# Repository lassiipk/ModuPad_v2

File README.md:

# ModuPad_v2

Improved Version of my ModuPad v1, With 3 Push Button rotary encoders, 25 Key switches, nice!nano MCU, and nice!view display.

---

---

## Schematic

---

## PCB

<!--  -->

---

## CAD

| Bottom | Full-CAD | Upper-Plate | 
| ------ | -------- | ----------- |
|  |  |  |

---

## BOM

**1 USD = 279.55 PKR**

> [Cart_Images](https://github.com/lassiipk/ModuPad_v2/tree/main/BOM/Cart_Images)
>
> [BOM.csv](https://github.com/lassiipk/ModuPad_v2/blob/main/BOM/BOM.csv)
>
> [BOM Folder](https://github.com/lassiipk/ModuPad_v2/tree/main/BOM/)

| Priority | Item                          | Qty | Unit Price | Shipping  | Total     | Notes               | Ordering Site    |
| -------- | ----------------------------- | --- | ---------- | --------- | --------- | ------------------- | ---------------- |
| 1        | PCB (Printed Circuit Board)   |  1  | US $8.40   | US $10.30 | US $18.70 | PCB                 | [JCLPCB](https://github.com/lassiipk/ModuPad_v2/blob/main/BOM/Cart_Images/JLCPCB_Screenshot-2026-03-17-183200.png) | 
| 2        | 3D Printed Case               |  1  | US $0.00   | US $12.00 | US $12.00 | Case / Knobs        | [#printing-legion](https://hackclub.enterprise.slack.com/archives/C083P4FJM46) |
| 3        | 3.7V 800mAh Battery           |  1  | US $1.79   | US $0.91  | US $2.71  | Wireless Connection | [Daraz](https://www.daraz.pk//products/i422858128-s2001359619.html?spm=a2o42.cart.0.0.af8f7d68YCkevZ&urlFlag=true) |
| 4        | nice!nano_v2.0 (NRF52840)     |  1  | US $3.30   | Free      | US $3.30  | MCU                 | [AliExpress](https://www.aliexpress.com/item/1005009516681283.html?spm=a2g0o.cart.0.0.7f5938da0jaPUj&mp=1&pdp_npi=6%40dis%21USD%21USD%203.30%21USD%203.30%21%21USD%203.30%21%21%21%40210156fc17737566309362930edfd4%2112000049341617471%21ct%21PK%216395474379%21%211%210%21) |
| 5        | 0.91 Inch 128x32 OLED Display |  1  | US $2.68   | Free      | US $2.68  | 128x32 OLED Display | [AliExpress](https://www.aliexpress.com/item/1005008640132638.html?spm=a2g0o.cart.0.0.7f5938da0jaPUj&mp=1&pdp_npi=6%40dis%21USD%21USD%202.84%21USD%202.68%21%21USD%202.68%21%21%21%40210156fc17737566288612823edfd4%2112000046056501838%21ct%21PK%216395474379%21%211%210%21) |
| 6        | Cherry MX Style Switches      |  1  | US $3.24   | Free      | US $3.24  | Switches            | [A;iExpress](https://www.aliexpress.com/item/1005010772946238.html?spm=a2g0o.cart.0.0.7f5938da0jaPUj&mp=1&pdp_npi=6%40dis%21USD%21USD%203.24%21USD%203.24%21%21USD%203.24%21%21%21%40210156fc17737566288612823edfd4%2112000053464130840%21ct%21PK%216395474379%21%211%210%21) |
| 7        | SK6812 MINI-E RGB LEDs        |  1  | US $3.69   | Free      | US $3.69  | RGB                 | [AliExpress](https://www.aliexpress.com/item/1005005193716172.html?spm=a2g0o.cart.0.0.744038da23sMVn&mp=1&pdp_npi=6%40dis%21USD%21USD%203.86%21USD%203.86%21%21USD%203.86%21%21%21%4021010d9017721244036344079e42d2%2112000032072424634%21ct%21PK%216395474379%21%211%210%21) |
| 8        | EC11 Rotary Encoders          |  1  | US $2.55   | Free      | US $2.55  | Rotary Encoders     | [AliExpress](https://www.aliexpress.com/item/1005007644083514.html?spm=a2g0o.cart.0.0.744038da23sMVn&mp=1&pdp_npi=6%40dis%21USD%21USD%202.65%21USD%202.65%21%21USD%202.65%21%21%21%4021010d9017721245116916843e42d2%2112000041630839426%21ct%21PK%216395474379%21%211%210%21) |
| 9        | 1N4148W SMD Diodes            |  1  | US $1.60   | Free      | US $1.60  | 28 diodes           | [AliExpress](https://www.aliexpress.com/item/1005007160563285.html?spm=a2g0o.cart.0.0.7f5938da0jaPUj&mp=1&pdp_npi=6%40dis%21USD%21USD%202.21%21USD%201.60%21%21USD%201.60%21%21%21%40210156fc17737566288612823edfd4%2112000039653324544%21ct%21PK%216395474379%21%211%210%21) |
| 10       | Kailh Hotswap Sockets         |  1  | US $2.82   | Free      | US $2.82  | Hotswap Sockets     | [AliExpress](https://www.aliexpress.com/item/1005009794038277.html?spm=a2g0o.cart.0.0.7f5938da0jaPUj&mp=1&pdp_npi=6%40dis%21USD%21USD%205.75%21USD%202.82%21%21USD%202.82%21%21%21%40210156fc17737566288612823edfd4%2112000050182431031%21ct%21PK%216395474379%21%211%210%21) |
| 11       | DSA Keycaps                   |  1  | US $5.00   | Free      | US $5.00  | 25 keycaps          | [AliExpress](https://www.aliexpress.com/item/32842379355.html?spm=a2g0o.cart.0.0.7f5938da0jaPUj&mp=1&pdp_npi=6%40dis%21USD%21USD%205.28%21USD%205.28%21%21USD%205.28%21%21%21%40210156fc17737566309362930edfd4%2110000001467765234%21ct%21PK%216395474379%21%211%210%21) |
| 12       | Power Switch                  |  1  | US $1.95   | Free      | US $1.95  | Power cutoff        | [AliExpress](https://www.aliexpress.com/item/1005007372534237.html?spm=a2g0o.cart.0.0.7f5938da0jaPUj&mp=1&pdp_npi=6%40dis%21USD%21USD%202.95%21USD%201.89%21%21USD%201.89%21%21%21%40210156fc17737566309362930edfd4%2112000040538852784%21ct%21PK%216395474379%21%211%210%21) |
| 13       | Battery Jack                  |  1  | US $1.66   | Free      | US $1.66  | Battery connection  | [AliExpress](https://www.aliexpress.com/item/1005004955655144.html?spm=a2g0o.cart.0.0.7f5938da0jaPUj&mp=1&pdp_npi=6%40dis%21USD%21USD%201.66%21USD%201.66%21%21USD%201.66%21%21%21%40210156fc17737566288612823edfd4%2112000031146362164%21ct%21PK%216395474379%21%211%210%21) |
| 14       | Reset Button                  |  1  | US $1.72   | Free      | US $1.72  | Reset For MCU       | [AliExpress](https://www.aliexpress.com/item/1005009331265393.html?spm=a2g0o.cart.0.0.7f5938da0jaPUj&mp=1&pdp_npi=6%40dis%21USD%21USD%201.72%21USD%201.72%21%21USD%201.72%21%21%21%40210156fc17737566288612823edfd4%2112000048778390261%21ct%21PK%216395474379%21%211%210%21) |
| 15       | 330R Resistor                 |  1  | US $2.27   | Free      | US $2.27  | Resistor            | [AliExpress](https://www.aliexpress.com/item/1005007043943146.html?spm=a2g0o.cart.0.0.7f5938da0jaPUj&mp=1&pdp_npi=6%40dis%21USD%21USD%202.88%21USD%202.28%21%21USD%202.28%21%21%21%40210156fc17737566288612823edfd4%2112000039203406400%21ct%21PK%216395474379%21%211%210%21) |
| 16       | 470UF Capacitor               |  1  | US $2.93   | Free      | US $2.93  | Capacitor           | [AliExpress](https://www.aliexpress.com/item/1005008498295736.html?spm=a2g0o.cart.0.0.7f5938da0jaPUj&mp=1&pdp_npi=6%40dis%21USD%21USD%203.05%21USD%202.85%21%21USD%202.85%21%21%21%40210156fc17737566288612823edfd4%2112000045532285458%21ct%21PK%216395474379%21%211%210%21) |
| 17       | M2/8mm Standoffs              |  1  | US $3.50   | Free      | US $3.50  | Mounting            | [AliExpress](https://www.aliexpress.com/item/1005008713639234.html?spm=a2g0o.cart.0.0.7f5938da0jaPUj&mp=1&pdp_npi=6%40dis%21USD%21USD%203.77%21USD%203.50%21%21USD%203.50%21%21%21%40210156fc17737566288612823edfd4%2112000046354950634%21ct%21PK%216395474379%21%211%210%21) |
| 18       | M2/4mm Screws                 |  1  | US $1.11   | Free      | US $1.11  | Mounting            | [AliExpress](https://www.aliexpress.com/item/1005003604942716.html?spm=a2g0o.cart.0.0.7f5938da0jaPUj&mp=1&pdp_npi=6%40dis%21USD%21USD%201.11%21USD%201.11%21%21USD%201.11%21%21%21%40210156fc17737566288612823edfd4%2112000026464812448%21ct%21PK%216395474379%21%211%210%21&pdp_ext_f=%7B%22cart2PdpParams%22%3A%7B%22pdpBusinessMode%22%3A%22retail%22%7D%7D) |

---    

> **AliExpress-Total = US $40.17** | *incl. Shipping*
>
> **#Printing-Legion = US $10** | *incl. Shipping*
>
> **JLCPCB-Total = US $20.00** | *incl. Shipping*
>
> **Daraz-Total = US $2.70** | *incl. Shipping*

**Total = US $73.44** | *incl. Shipping*

---

## Timeline

**Project Started:** 05-Jan 2026 | 3:40PM

**Project Ended:** 14-Feb-2026 | 5:00 PM

**Project README Entry Written:** 17-Feb 2026 | 9:00 PM

**Project Intital Submit:** Feb 17th at 9:21 PM

**Project Second submission:** Feb 27th at N/a AM (**@alexren** requested changes, Feb 19th at 2:48 AM) BOM is optimised as much I was able to!

---

## License

This project is open‑source and intended for educational and personal use.

---

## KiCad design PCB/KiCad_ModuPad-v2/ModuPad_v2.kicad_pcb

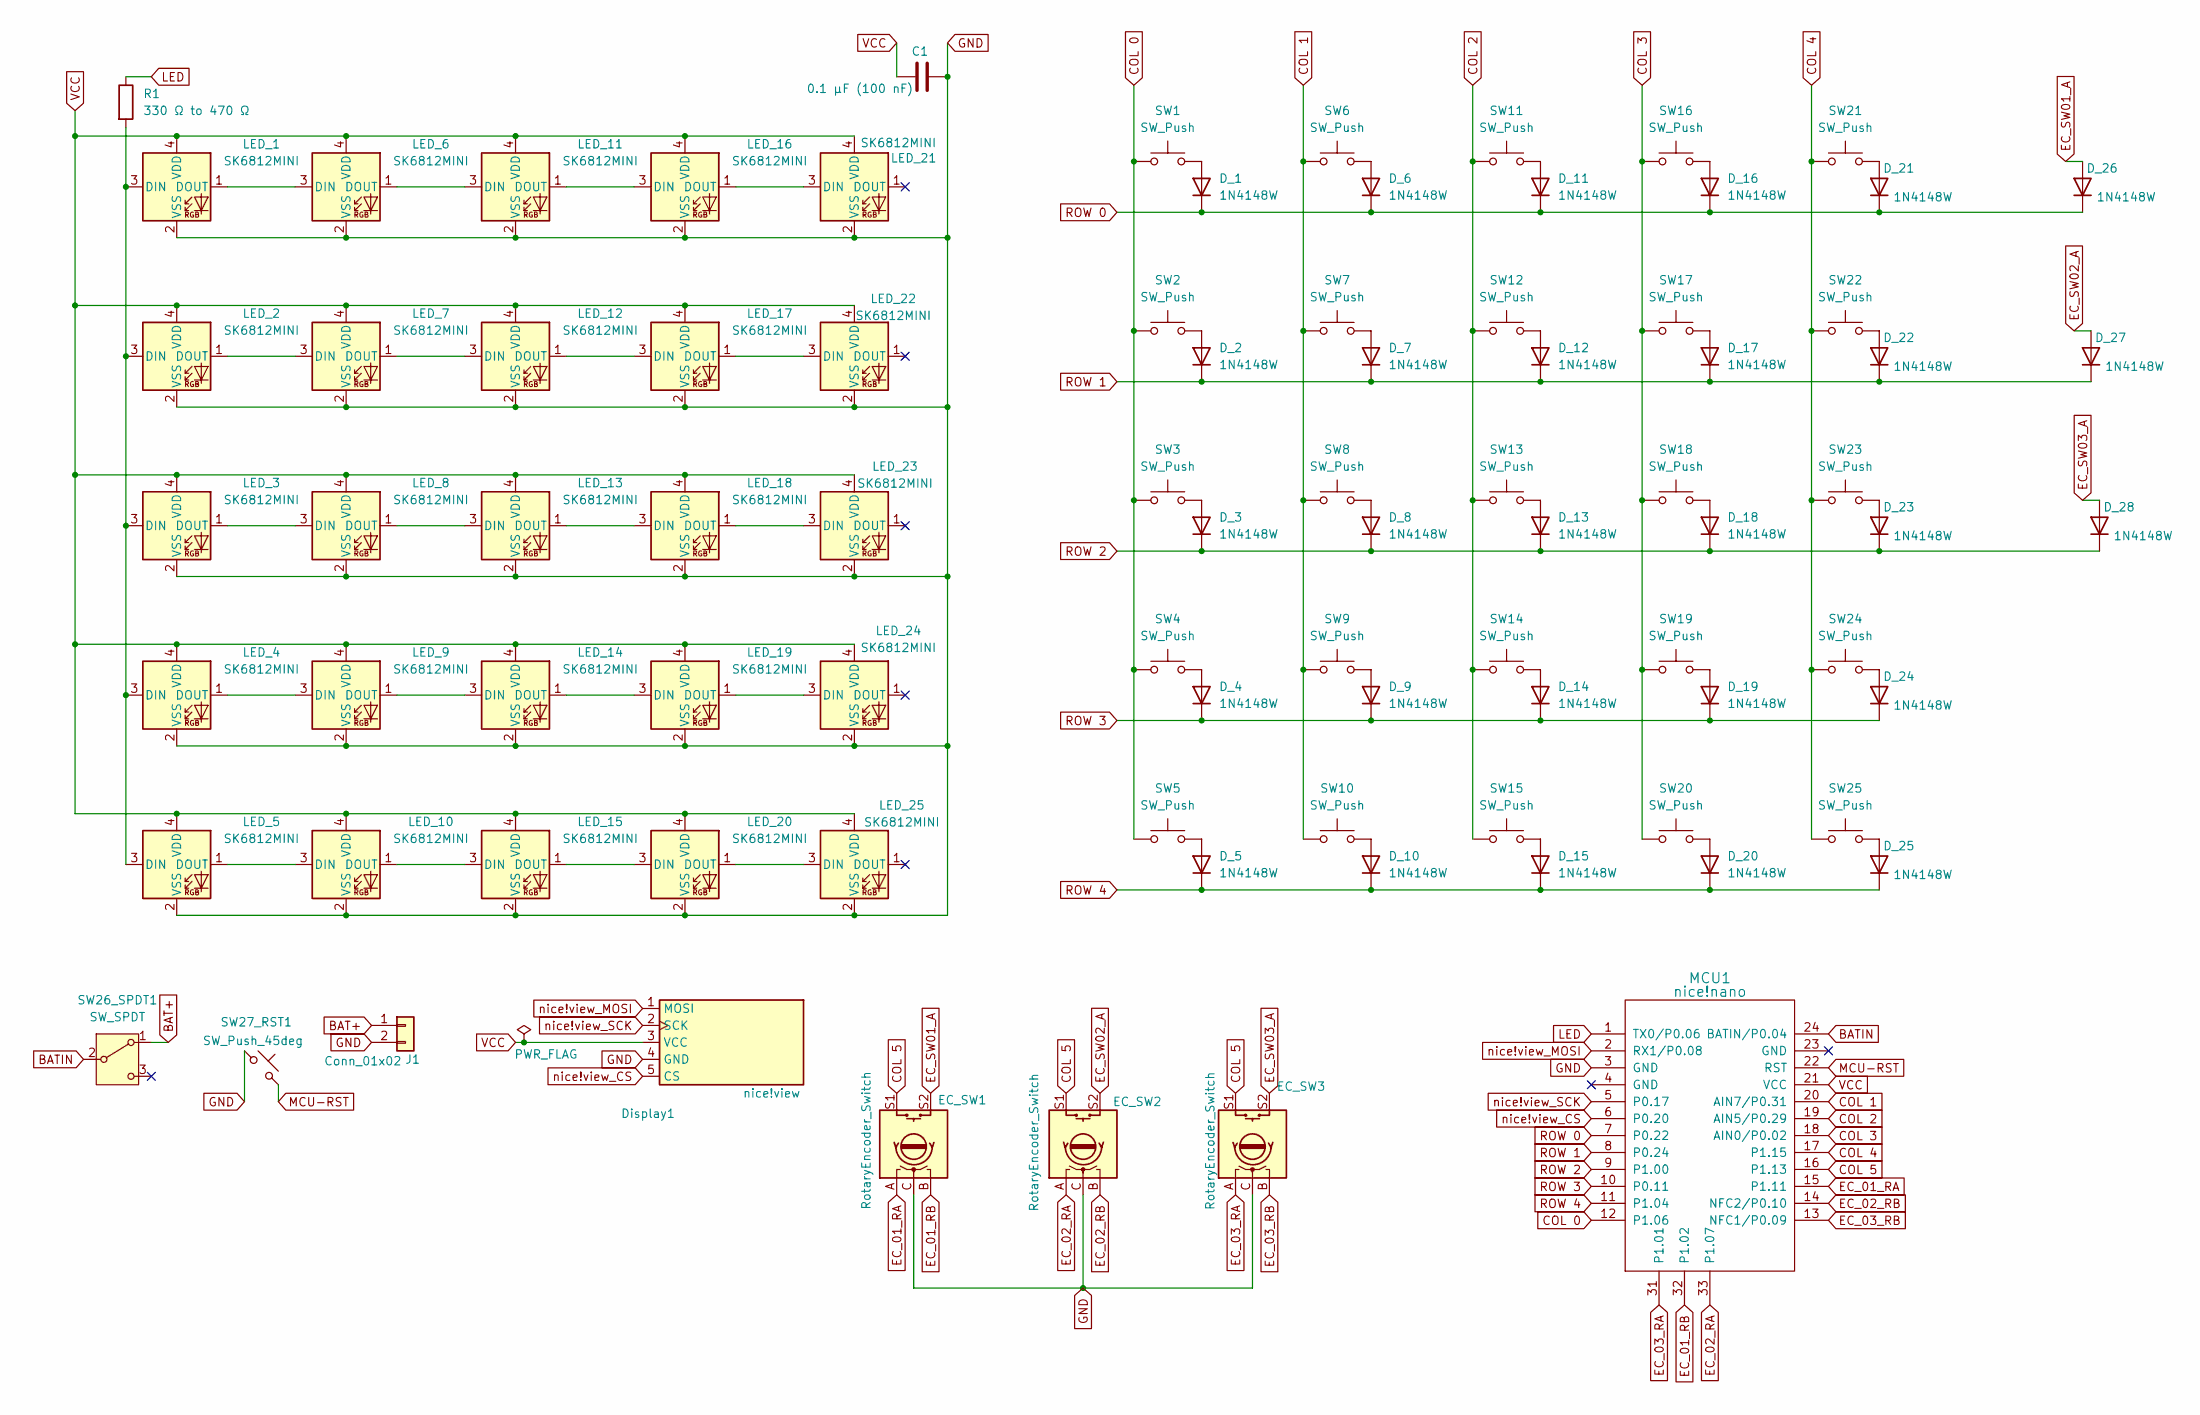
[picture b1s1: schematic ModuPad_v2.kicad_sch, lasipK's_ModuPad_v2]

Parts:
C1: 0.1 µF (100 nF); C_0603_1608Metric
D_1, D_2, D_3, D_4, D_5, D_6, D_7, D_8, D_9, D_10, D_11, D_12, D_13, D_14, D_15, D_16, D_17, D_18, D_19, D_20, D_21, D_22, D_23, D_24, D_25, D_26, D_27, D_28: 1N4148W; D_SOD-123
Display1: nice!view; nice_view
EC_SW1, EC_SW2, EC_SW3: RotaryEncoder_Switch; RotaryEncoder_Alps_EC11E-Switch_Vertical_H20mm_CircularMoun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
J1: Conn_01x02; JST_PH_S2B-PH-K_02x2.00mm_Angled
LED_1, LED_2, LED_3, LED_4, LED_5, LED_6, LED_7, LED_8, LED_9, LED_10, LED_11, LED_12, LED_13, LED_14, LED_15, LED_16, LED_17, LED_18, LED_19, LED_20, LED_21, LED_22, LED_23, LED_24, LED_25: SK6812MINI; SK6812MINI-E
MCU1: nice!nano; nice_nano
R1: 330 Ω to 470 Ω; R_0603_1608Metric_Pad0.98x0.95mm_HandSolder
SW1, SW2, SW3, SW4, SW5, SW6, SW7, SW8, SW9, SW10, SW11, SW12, SW13, SW14, SW15, SW16, SW17, SW18, SW19, SW20, SW21, SW22, SW23, SW24, SW25: SW_Push; SW_MX_HS_CPG151101S11_1u
SW26_SPDT1: SW_SPDT; SPDT_C128955
SW27_RST1: SW_Push_45deg; Panasonic_EVQPUL_EVQPUC

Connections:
BATIN: MCU1.24 (BATIN/P0.04), SW26_SPDT1.2 (B); also elsewhere on the board
COL 0: MCU1.12 (P1.06), SW1.1, SW2.1, SW3.1, SW4.1, SW5.1
COL 1: MCU1.20 (AIN7/P0.31), SW6.1, SW7.1, SW8.1, SW9.1, SW10.1
COL 2: MCU1.19 (AIN5/P0.29), SW11.1, SW12.1, SW13.1, SW14.1, SW15.1
COL 3: MCU1.18 (AIN0/P0.02), SW16.1, SW17.1, SW18.1, SW19.1, SW20.1
COL 4: MCU1.17 (P1.15), SW21.1, SW22.1, SW23.1, SW24.1, SW25.1
COL 5: EC_SW1.S1, EC_SW2.S1, EC_SW3.S1, MCU1.16 (P1.13)
EC_01_RA: EC_SW1.A, MCU1.15 (P1.11)
EC_01_RB: EC_SW1.B, MCU1.32 (P1.02)
EC_02_RA: EC_SW2.A, MCU1.33 (P1.07)
EC_02_RB: EC_SW2.B, MCU1.14 (NFC2/P0.10)
EC_03_RA: EC_SW3.A, MCU1.31 (P1.01)
EC_03_RB: EC_SW3.B, MCU1.13 (NFC1/P0.09)
EC_SW01_A: D_26.2 (A), EC_SW1.S2
EC_SW02_A: D_27.2 (A), EC_SW2.S2
EC_SW03_A: D_28.2 (A), EC_SW3.S2
LED: MCU1.1 (TX0/P0.06), R1.1
unnamed: D_1.2 (A), SW1.2
unnamed: D_2.2 (A), SW2.2
unnamed: D_3.2 (A), SW3.2
unnamed: D_4.2 (A), SW4.2
unnamed: D_5.2 (A), SW5.2
unnamed: D_6.2 (A), SW6.2
unnamed: D_7.2 (A), SW7.2
unnamed: D_8.2 (A), SW8.2
unnamed: D_9.2 (A), SW9.2
unnamed: D_10.2 (A), SW10.2
unnamed: D_11.2 (A), SW11.2
unnamed: D_12.2 (A), SW12.2
unnamed: D_13.2 (A), SW13.2
unnamed: D_14.2 (A), SW14.2
unnamed: D_15.2 (A), SW15.2
unnamed: D_16.2 (A), SW16.2
unnamed: D_17.2 (A), SW17.2
unnamed: D_18.2 (A), SW18.2
unnamed: D_19.2 (A), SW19.2
unnamed: D_20.2 (A), SW20.2
unnamed: D_21.2 (A), SW21.2
unnamed: D_22.2 (A), SW22.2
unnamed: D_23.2 (A), SW23.2
unnamed: D_24.2 (A), SW24.2
unnamed: D_25.2 (A), SW25.2
unnamed: Display1.1 (MOSI), MCU1.2 (RX1/P0.08)
unnamed: LED_1.3 (DIN), LED_2.3 (DIN), LED_3.3 (DIN), LED_4.3 (DIN), LED_5.3 (DIN), R1.2
unnamed: LED_1.1 (DOUT), LED_6.3 (DIN)
unnamed: LED_2.1 (DOUT), LED_7.3 (DIN)
unnamed: LED_3.1 (DOUT), LED_8.3 (DIN)
unnamed: LED_4.1 (DOUT), LED_9.3 (DIN)
unnamed: LED_5.1 (DOUT), LED_10.3 (DIN)
unnamed: LED_10.1 (DOUT), LED_15.3 (DIN)
unnamed: LED_6.1 (DOUT), LED_11.3 (DIN)
unnamed: LED_11.1 (DOUT), LED_16.3 (DIN)
unnamed: LED_7.1 (DOUT), LED_12.3 (DIN)
unnamed: LED_12.1 (DOUT), LED_17.3 (DIN)
unnamed: LED_8.1 (DOUT), LED_13.3 (DIN)
unnamed: LED_13.1 (DOUT), LED_18.3 (DIN)
unnamed: LED_9.1 (DOUT), LED_14.3 (DIN)
unnamed: LED_14.1 (DOUT), LED_19.3 (DIN)
unnamed: LED_15.1 (DOUT), LED_20.3 (DIN)
unnamed: LED_16.1 (DOUT), LED_21.3 (DIN)
unnamed: LED_17.1 (DOUT), LED_22.3 (DIN)
unnamed: LED_18.1 (DOUT), LED_23.3 (DIN)
unnamed: LED_19.1 (DOUT), LED_24.3 (DIN)
unnamed: LED_20.1 (DOUT), LED_25.3 (DIN)
ROW 0: D_1.1 (K), D_6.1 (K), D_11.1 (K), D_16.1 (K), D_21.1 (K), D_26.1 (K), MCU1.7 (P0.22)
ROW 1: D_2.1 (K), D_7.1 (K), D_12.1 (K), D_17.1 (K), D_22.1 (K), D_27.1 (K), MCU1.8 (P0.24)
ROW 2: D_3.1 (K), D_8.1 (K), D_13.1 (K), D_18.1 (K), D_23.1 (K), D_28.1 (K), MCU1.9 (P1.00)
ROW 3: D_4.1 (K), D_9.1 (K), D_14.1 (K), D_19.1 (K), D_24.1 (K), MCU1.10 (P0.11)
ROW 4: D_5.1 (K), D_10.1 (K), D_15.1 (K), D_20.1 (K), D_25.1 (K), MCU1.11 (P1.04)
RST: MCU1.22 (RST), SW27_RST1.2
SCL: Display1.5 (CS), MCU1.6 (P0.20); also elsewhere on the board
SDA: Display1.2 (SCK), MCU1.5 (P0.17); also elsewhere on the board

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
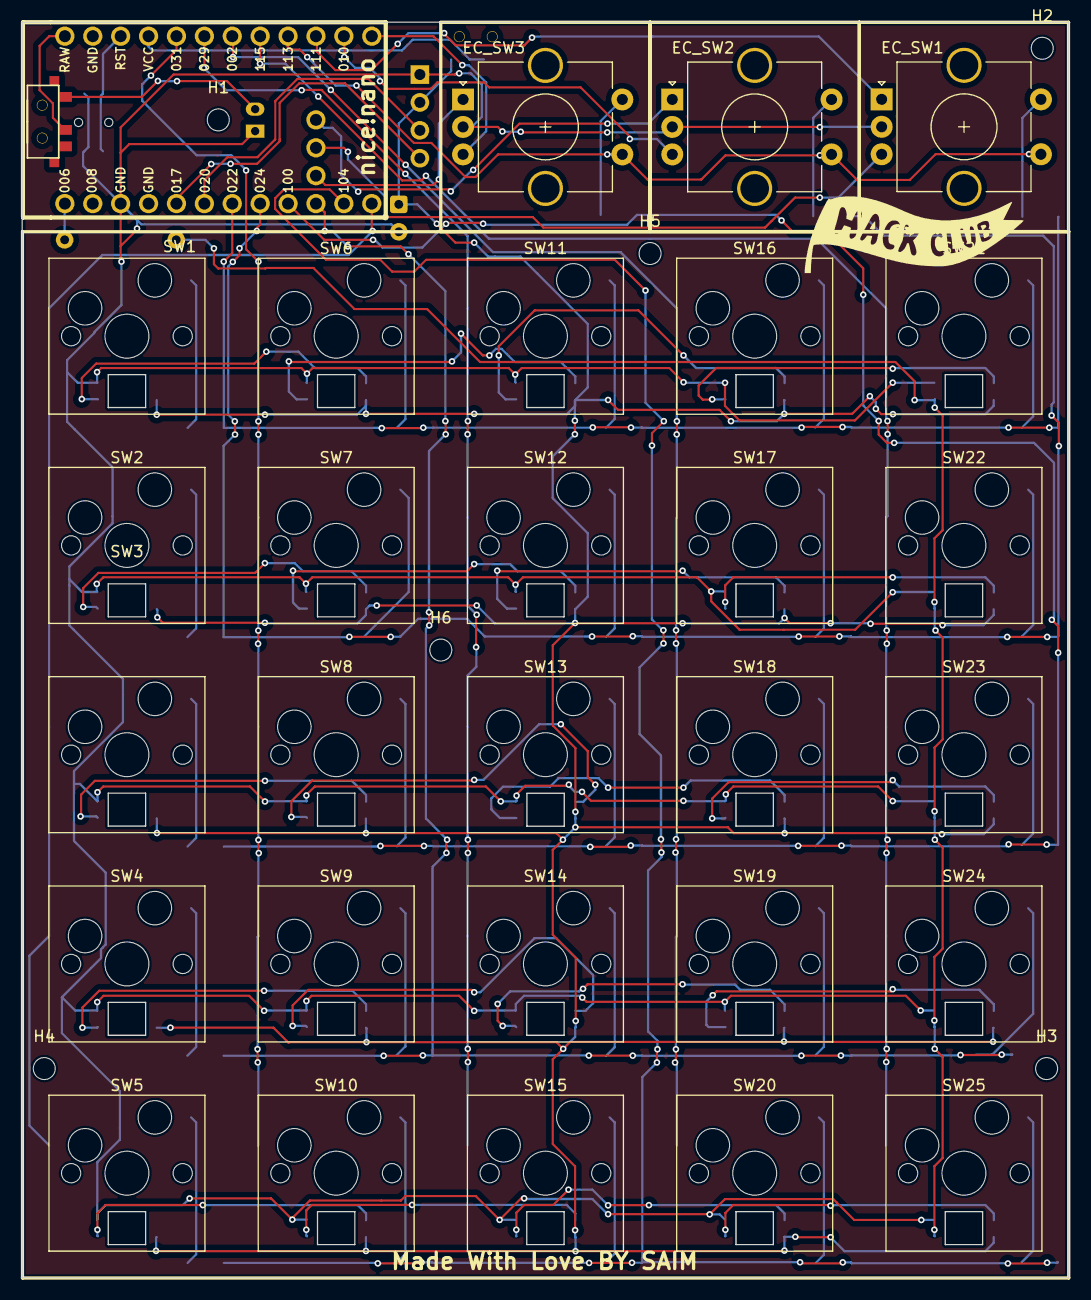
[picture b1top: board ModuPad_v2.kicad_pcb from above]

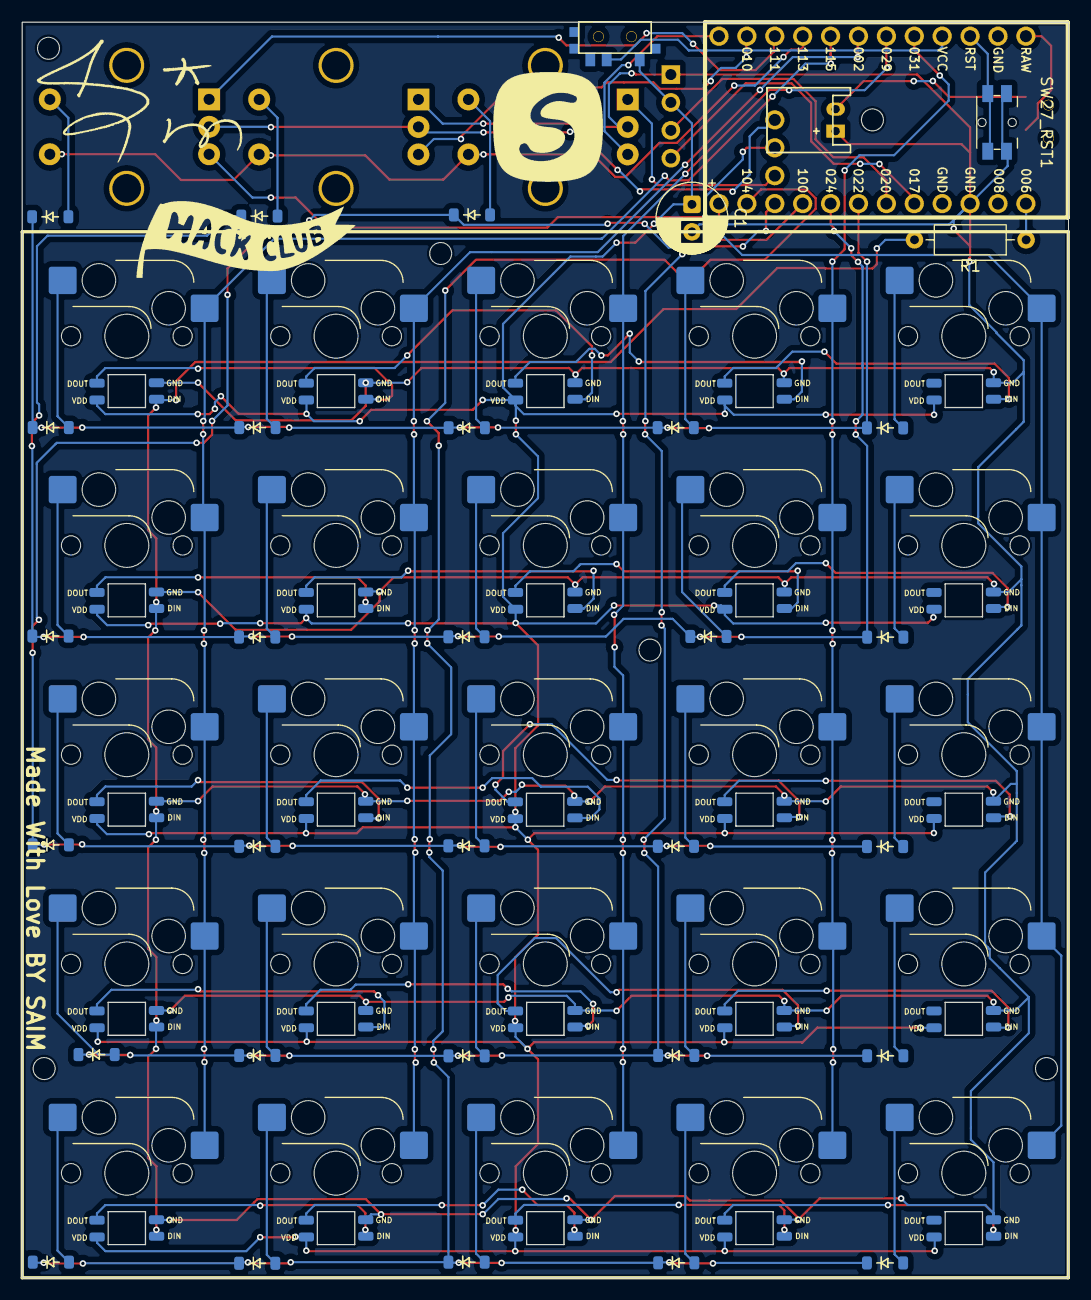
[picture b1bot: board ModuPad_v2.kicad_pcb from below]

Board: 2 copper layers, 95.3 x 114.3 mm, 95 parts (32 on the bottom side), 75 nets.

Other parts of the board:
BAT-Power-Switch_SPDT1: SW_SPDT; SPDT_C128955
H1, H2, H3, H4, H5, H6: MountingHole; MountingHole_2mm
J2: OLED_128x32
LED-OLED-Power-Switch_SPDT2: SW_SPDT; SPDT_C128955

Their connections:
BATIN: BAT-Power-Switch_SPDT1.2 (B); also elsewhere on the board
SCL: J2.3 (SCL); also elsewhere on the board
SDA: J2.4 (SDA); also elsewhere on the board

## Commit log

2026-01-18 Rename ModuPad-v2_Journa_01.md to ModuPad-v2_Journal_01.md
2026-01-20 Rename ModuPad-v2-Journal-01.md to ModuPad-v2_Journal-01.md
2026-01-23 Rename ModuPad-v2_Jouranal-05.md to ModuPad-v2_Journal-05.md
2026-02-14 Project Uploded
2026-02-14 Deleted unnessorry gerber files
2026-02-15 Add Gerber files for ModuPad v2 PCB
    Add Gerber outputs for the ModuPad_v2 KiCad project to PCB/KiCad_ModuPad-v2/Gerber. Files include an archive (Gerber.rar) on 2026-02-15 for PCB fabrication.
2026-02-15 Split and reformat BOM into PKR and USD files
2026-02-15 Remove BOM markdown files
    Delete BOM/BOM.md, BOM/BOM_PKR.md, and BOM/BOM_USD.md which contained bill-of-materials for the mechanical keyboard build. Clean up repository by removing redundant or outdated BOM documents.
2026-02-15 Add BOM files for mechanical keyboard build
    Add Bill of Materials for the mechanical keyboard project: BOM/BOM.md (combined PKR & USD lists) and separate BOM/BOM_PKR.md and BOM/BOM_USD.md. Each file enumerates components, quantities, unit pric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
2026-02-17 Replace BOM with markdown variants and add assets
    Remove legacy BOM files and add structured BOM Markdown files (PKR, USD, combined PKR+USD) and a links file. Add BOM/cart screenshots and a BOM image, plus CAD knob assets (RAR, renamed STEP/STL) and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
2026-02-17 Update README with project details and images
    Added detailed project information including schematic, PCB, CAD, BOM, timeline, and license.
2026-02-17 Revise project timeline details in README
    Updated project timeline entries with specific timestamps and improved formatting.
2026-02-26 Consolidate BOM into single file
2026-02-26 Revise BOM pricing and update timeline
2026-03-05 Add flashing instructions.md and removed unnecessary PCB files.
2026-03-05 Create BOM.csv inside BOM Folder
2026-03-10 Update BOM and PCB
2026-03-17 Bom Update
2026-03-17 Update BOM
2026-03-17 Update Cart / Rename
2026-03-19 Create
2026-05-21 Moved Old-Design to /Old-Design Folder
    Moved Old-Design to /Old-Design Folder, Because The PCB is Redesigned, The Measurements are Changed.
